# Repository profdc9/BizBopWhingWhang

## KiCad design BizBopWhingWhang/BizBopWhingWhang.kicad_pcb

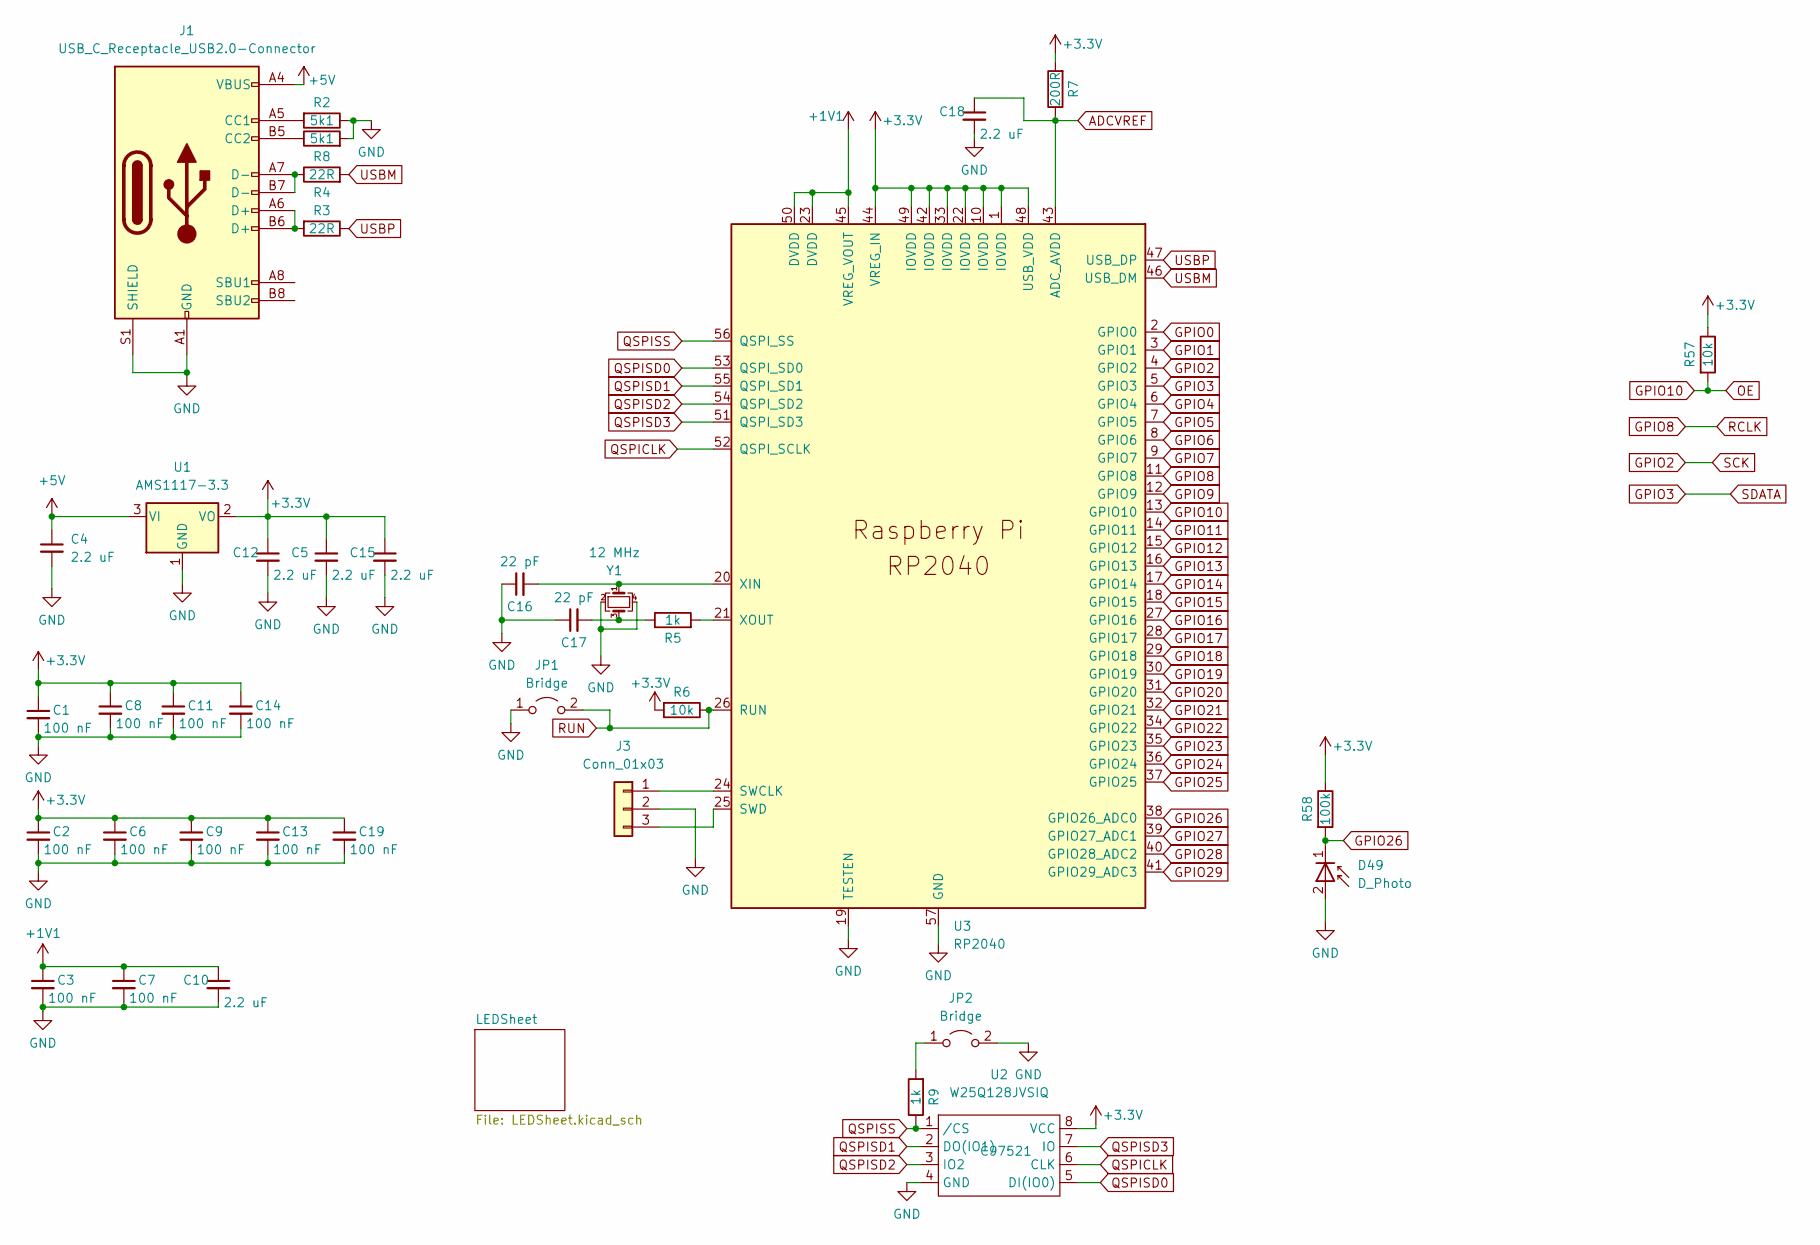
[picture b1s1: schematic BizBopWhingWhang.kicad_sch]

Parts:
C1, C2, C3, C6, C7, C8, C9, C11, C13, C14, C19: 100 nF; C_0402_1005Metric; LCSC C307331
C4, C5, C10, C12, C15, C18: 2.2 uF; C_0603_1608Metric; LCSC C23630
C16, C17: 22 pF; C_0402_1005Metric; LCSC C1555
D49: D_Photo; PD-1522CTR8; LCSC C146236
J1: USB_C_Receptacle_USB2.0-Connector; TYPE-C-31-M-12; LCSC C165948
J3: Conn_01x03; PinHeader_1x03_P2.54mm_Vertical
JP1, JP2: Bridge; PinHeader_1x02_P2.54mm_Vertical
R2, R8: 5k1; R_0603_1608Metric_Pad0.98x0.95mm_HandSolder; LCSC C23186
R3, R4: 22R; R_0603_1608Metric_Pad0.98x0.95mm_HandSolder; LCSC C23345
R5: 1k; R_0402_1005Metric; LCSC C11702
R6, R57: 10k; R_0603_1608Metric_Pad0.98x0.95mm_HandSolder; LCSC C25804
R7: 200R; R_0603_1608Metric_Pad0.98x0.95mm_HandSolder; LCSC C22962
R9: 1k; R_0603_1608Metric_Pad0.98x0.95mm_HandSolder; LCSC C21190
R58: 100k; R_0603_1608Metric_Pad0.98x0.95mm_HandSolder; LCSC C25803
U1: AMS1117-3.3; SOT-223-3_TabPin2; LCSC C6186
U2: W25Q128JVSIQ; SOIC-8_3.9x4.9mm_P1.27mm_mod; LCSC C97521
U3: RP2040; QFN-56-1EP_7x7mm_P0.4mm_EP3.2x3.2mm; LCSC C2040
Y1: 12 MHz; Crystal_SMD_3225-4Pin_3.2x2.5mm; LCSC C9002

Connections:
+1V1: C3.1, C7.1, C10.1, U3.23 (DVDD), U3.45 (VREG_VOUT), U3.50 (DVDD)
+3.3V: C1.1, C2.1, C5.1, C6.1, C8.1, C9.1, C11.1, C12.1, C13.1, C14.1, C15.1, C19.1, R6.2, R7.2, R57.1, R58.1, U1.2 (VO), U2.8 (VCC), U3.1 (IOVDD), U3.10 (IOVDD), U3.22 (IOVDD), U3.33 (IOVDD), U3.42 (IOVDD), U3.44 (VREG_IN), U3.48 (USB_VDD), U3.49 (IOVDD); also elsewhere on the board
+5V: C4.1, J1.A4 (VBUS), J1.A9 (VBUS), J1.B4 (VBUS), J1.B9 (VBUS), U1.3 (VI)
ADCVREF: C18.1, R7.1, U3.43 (ADC_AVDD)
GND: C1.2, C2.2, C3.2, C4.2, C5.2, C6.2, C7.2, C8.2, C9.2, C10.2, C11.2, C12.2, C13.2, C14.2, C15.2, C16.1, C17.1, C18.2, C19.2, D49.2 (A), J1.A1 (GND), J1.A12 (GND), J1.B1 (GND), J1.B12 (GND), J1.S1 (SHIELD), J3.2, JP1.1 (A), JP2.2 (B), R2.1, R8.2, U1.1 (GND), U2.4 (GND), U3.19 (TESTEN), U3.57 (GND), Y1.2, Y1.4; also elsewhere on the board
GPIO0: U3.2 (GPIO0)
GPIO1: U3.3 (GPIO1)
GPIO2: U3.4 (GPIO2); also elsewhere on the board
GPIO3: U3.5 (GPIO3); also elsewhere on the board
GPIO4: U3.6 (GPIO4)
GPIO5: U3.7 (GPIO5)
GPIO6: U3.8 (GPIO6)
GPIO7: U3.9 (GPIO7)
GPIO8: U3.11 (GPIO8); also elsewhere on the board
GPIO9: U3.12 (GPIO9)
GPIO10: R57.2, U3.13 (GPIO10); also elsewhere on the board
GPIO11: U3.14 (GPIO11)
GPIO12: U3.15 (GPIO12)
GPIO13: U3.16 (GPIO13)
GPIO14: U3.17 (GPIO14)
GPIO15: U3.18 (GPIO15)
GPIO16: U3.27 (GPIO16)
GPIO17: U3.28 (GPIO17)
GPIO18: U3.29 (GPIO18)
GPIO19: U3.30 (GPIO19)
GPIO20: U3.31 (GPIO20)
GPIO21: U3.32 (GPIO21)
GPIO22: U3.34 (GPIO22)
GPIO23: U3.35 (GPIO23)
GPIO24: U3.36 (GPIO24)
GPIO25: U3.37 (GPIO25)
GPIO26: D49.1 (K), R58.2, U3.38 (GPIO26_ADC0)
GPIO27: U3.39 (GPIO27_ADC1)
GPIO28: U3.40 (GPIO28_ADC2)
GPIO29: U3.41 (GPIO29_ADC3)
unnamed: C16.2, U3.20 (XIN), Y1.1
unnamed: C17.2, R5.1, Y1.3
unnamed: J1.A5 (CC1), R2.2
unnamed: J1.A6 (D+), J1.B6 (D+), R3.2
unnamed: J1.A7 (D-), J1.B7 (D-), R4.1
unnamed: J1.B5 (CC2), R8.1
unnamed: J3.1, U3.24 (SWCLK)
unnamed: J3.3, U3.25 (SWD)
unnamed: JP2.1 (A), R9.2
unnamed: R5.2, U3.21 (XOUT)
QSPICLK: U2.6 (CLK), U3.52 (QSPI_SCLK)
QSPISD0: U2.5 (DI(IO0)), U3.53 (QSPI_SD0)
QSPISD1: U2.2 (DO(IO1)), U3.55 (QSPI_SD1)
QSPISD2: U2.3 (IO2), U3.54 (QSPI_SD2)
QSPISD3: U2.7 (IO), U3.51 (QSPI_SD3)
QSPISS: R9.1, U2.1 (/CS), U3.56 (QSPI_SS)
RUN: JP1.2 (B), R6.1, U3.26 (RUN)
USBM: R4.2, U3.46 (USB_DM)
USBP: R3.1, U3.47 (USB_DP)

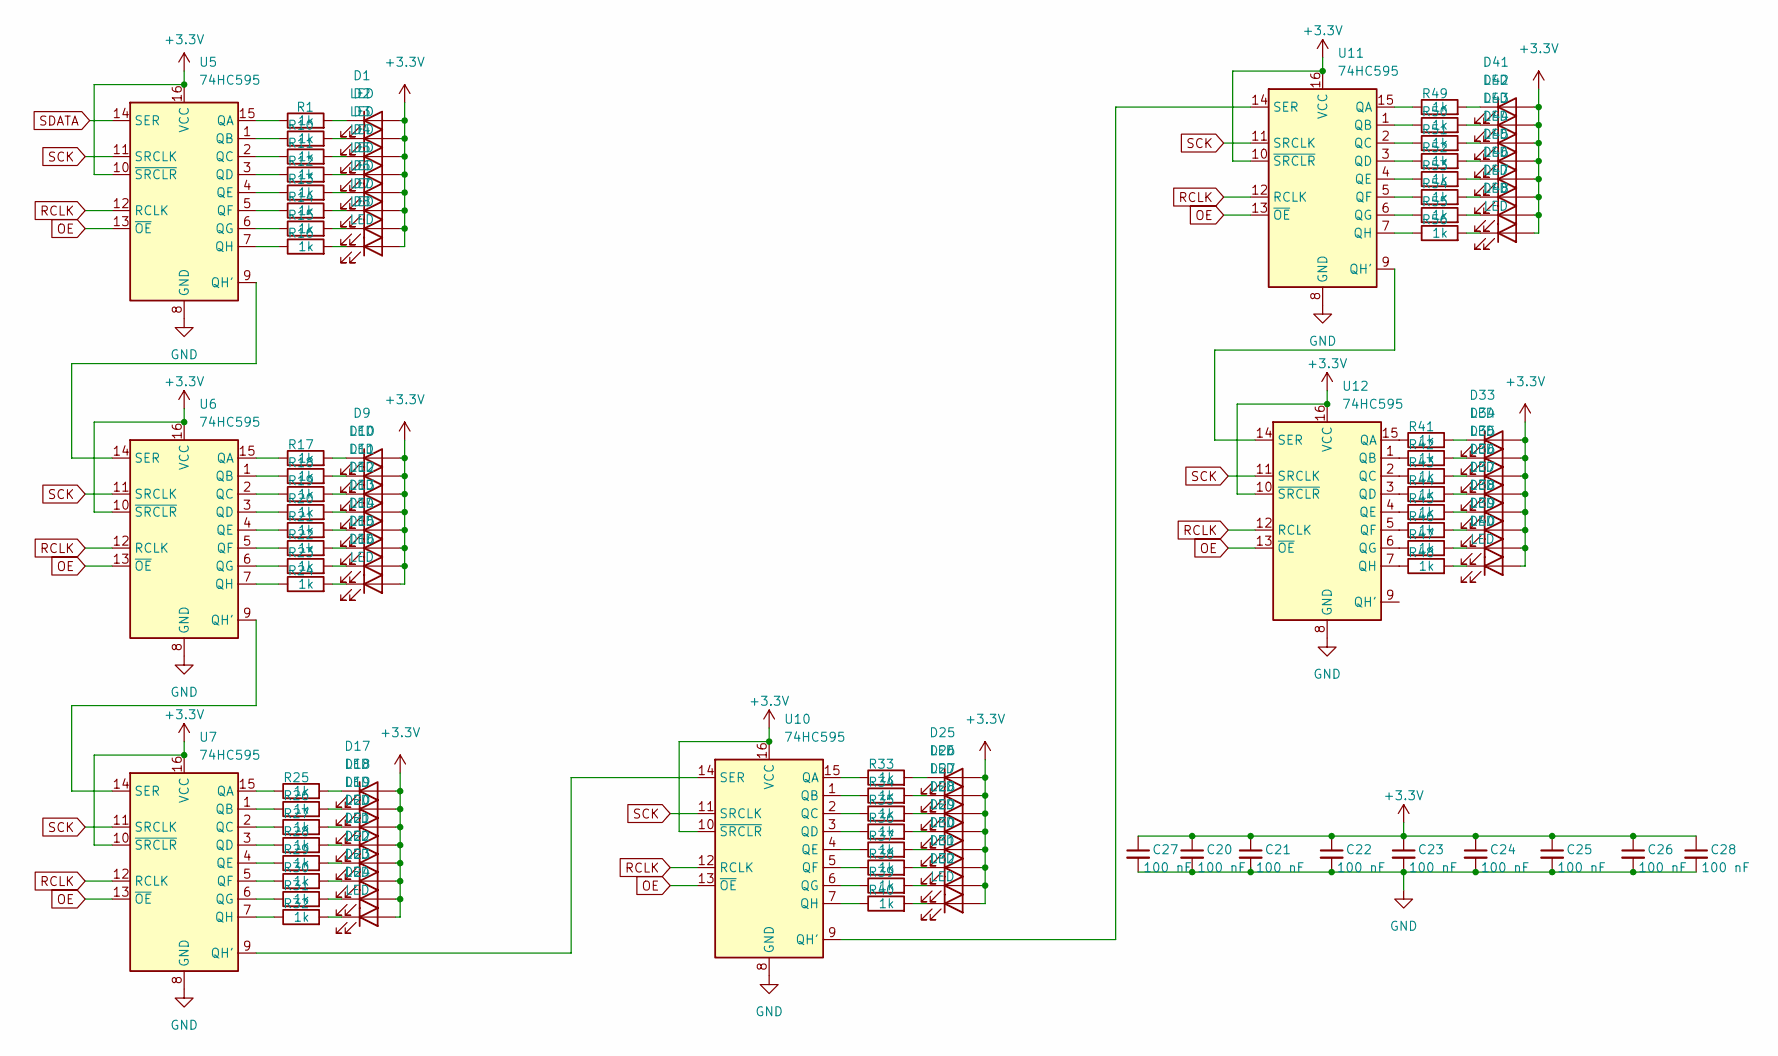
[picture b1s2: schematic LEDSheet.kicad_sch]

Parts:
C20, C21, C22, C23, C24, C25, C26, C27, C28: 100 nF; C_0402_1005Metric; LCSC C307331
D1, D2, D3, D4, D5, D6, D7, D8, D9, D10, D11, D12, D13, D14, D15, D16, D17, D18, D19, D20, D21, D22, D23, D24, D25, D26, D27, D28, D29, D30, D31, D32, D33, D34, D35, D36, D37, D38, D39, D40, D41, D42, D43, D44, D45, D46, D47, D48: LED; LED_0402_1005Metric; LCSC C779449
R1, R10, R11, R12, R13, R14, R15, R16, R17, R18, R19, R20, R21, R22, R23, R24, R25, R26, R27, R28, R29, R30, R31, R32, R33, R34, R35, R36, R37, R38, R39, R40, R41, R42, R43, R44, R45, R46, R47, R48, R49, R50, R51, R52, R53, R54, R55, R56: 1k; R_0402_1005Metric; LCSC C11702
U5, U6, U7, U10, U11, U12: 74HC595; TSSOP-16_4.4x5mm_P0.65mm; LCSC C20613246

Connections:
+3.3V: C20.1, C21.1, C22.1, C23.1, C24.1, C25.1, C26.1, C27.1, C28.1, D1.2 (A), D2.2 (A), D3.2 (A), D4.2 (A), D5.2 (A), D6.2 (A), D7.2 (A), D8.2 (A), D9.2 (A), D10.2 (A), D11.2 (A), D12.2 (A), D13.2 (A), D14.2 (A), D15.2 (A), D16.2 (A), D17.2 (A), D18.2 (A), D19.2 (A), D20.2 (A), D21.2 (A), D22.2 (A), D23.2 (A), D24.2 (A), D25.2 (A), D26.2 (A), D27.2 (A), D28.2 (A), D29.2 (A), D30.2 (A), D31.2 (A), D32.2 (A), D33.2 (A), D34.2 (A), D35.2 (A), D36.2 (A), D37.2 (A), D38.2 (A), D39.2 (A), D40.2 (A), D41.2 (A), D42.2 (A), D43.2 (A), D44.2 (A), D45.2 (A), D46.2 (A), D47.2 (A), D48.2 (A), U5.10 (~SRCLR), U5.16 (VCC), U6.10 (~SRCLR), U6.16 (VCC), U7.10 (~SRCLR), U7.16 (VCC), U10.10 (~SRCLR), U10.16 (VCC), U11.10 (~SRCLR), U11.16 (VCC), U12.10 (~SRCLR), U12.16 (VCC); also elsewhere on the board
GND: C20.2, C21.2, C22.2, C23.2, C24.2, C25.2, C26.2, C27.2, C28.2, U5.8 (GND), U6.8 (GND), U7.8 (GND), U10.8 (GND), U11.8 (GND), U12.8 (GND); also elsewhere on the board
GPIO2: U5.11 (SRCLK), U6.11 (SRCLK), U7.11 (SRCLK), U10.11 (SRCLK), U11.11 (SRCLK), U12.11 (SRCLK); also elsewhere on the board
GPIO3: U5.14 (SER); also elsewhere on the board
GPIO8: U5.12 (RCLK), U6.12 (RCLK), U7.12 (RCLK), U10.12 (RCLK), U11.12 (RCLK), U12.12 (RCLK); also elsewhere on the board
GPIO10: U5.13 (~OE), U6.13 (~OE), U7.13 (~OE), U10.13 (~OE), U11.13 (~OE), U12.13 (~OE); also elsewhere on the board
unnamed: D1.1 (K), R1.2
unnamed: D2.1 (K), R10.2
unnamed: D3.1 (K), R11.2
unnamed: D4.1 (K), R12.2
unnamed: D5.1 (K), R13.2
unnamed: D6.1 (K), R14.2
unnamed: D7.1 (K), R15.2
unnamed: D8.1 (K), R16.2
unnamed: D9.1 (K), R17.2
unnamed: D10.1 (K), R18.2
unnamed: D11.1 (K), R19.2
unnamed: D12.1 (K), R20.2
unnamed: D13.1 (K), R21.2
unnamed: D14.1 (K), R22.2
unnamed: D15.1 (K), R23.2
unnamed: D16.1 (K), R24.2
unnamed: D17.1 (K), R25.2
unnamed: D18.1 (K), R26.2
unnamed: D19.1 (K), R27.2
unnamed: D20.1 (K), R28.2
unnamed: D21.1 (K), R29.2
unnamed: D22.1 (K), R30.2
unnamed: D23.1 (K), R31.2
unnamed: D24.1 (K), R32.2
unnamed: D25.1 (K), R33.2
unnamed: D26.1 (K), R34.2
unnamed: D27.1 (K), R35.2
unnamed: D28.1 (K), R36.2
unnamed: D29.1 (K), R37.2
unnamed: D30.1 (K), R38.2
unnamed: D31.1 (K), R39.2
unnamed: D32.1 (K), R40.2
unnamed: D33.1 (K), R41.2
unnamed: D34.1 (K), R42.2
unnamed: D35.1 (K), R43.2
unnamed: D36.1 (K), R44.2
unnamed: D37.1 (K), R45.2
unnamed: D38.1 (K), R46.2
unnamed: D39.1 (K), R47.2
unnamed: D40.1 (K), R48.2
unnamed: D41.1 (K), R49.2
unnamed: D42.1 (K), R50.2
unnamed: D43.1 (K), R51.2
unnamed: D44.1 (K), R52.2
unnamed: D45.1 (K), R53.2
unnamed: D46.1 (K), R54.2
unnamed: D47.1 (K), R55.2
unnamed: D48.1 (K), R56.2
unnamed: R1.1, U5.15 (QA)
unnamed: R10.1, U5.1 (QB)
unnamed: R11.1, U5.2 (QC)
unnamed: R12.1, U5.3 (QD)
unnamed: R13.1, U5.4 (QE)
unnamed: R14.1, U5.5 (QF)
unnamed: R15.1, U5.6 (QG)
unnamed: R16.1, U5.7 (QH)
unnamed: R17.1, U6.15 (QA)
unnamed: R18.1, U6.1 (QB)
unnamed: R19.1, U6.2 (QC)
unnamed: R20.1, U6.3 (QD)
unnamed: R21.1, U6.4 (QE)
unnamed: R22.1, U6.5 (QF)
unnamed: R23.1, U6.6 (QG)
unnamed: R24.1, U6.7 (QH)
unnamed: R25.1, U7.15 (QA)
unnamed: R26.1, U7.1 (QB)
unnamed: R27.1, U7.2 (QC)
unnamed: R28.1, U7.3 (QD)
unnamed: R29.1, U7.4 (QE)
unnamed: R30.1, U7.5 (QF)
unnamed: R31.1, U7.6 (QG)
unnamed: R32.1, U7.7 (QH)
unnamed: R33.1, U10.15 (QA)
unnamed: R34.1, U10.1 (QB)
unnamed: R35.1, U10.2 (QC)
unnamed: R36.1, U10.3 (QD)
unnamed: R37.1, U10.4 (QE)
unnamed: R38.1, U10.5 (QF)
unnamed: R39.1, U10.6 (QG)
unnamed: R40.1, U10.7 (QH)
unnamed: R41.1, U12.15 (QA)
unnamed: R42.1, U12.1 (QB)
unnamed: R43.1, U12.2 (QC)
unnamed: R44.1, U12.3 (QD)
unnamed: R45.1, U12.4 (QE)
unnamed: R46.1, U12.5 (QF)
unnamed: R47.1, U12.6 (QG)
unnamed: R48.1, U12.7 (QH)
unnamed: R49.1, U11.15 (QA)
unnamed: R50.1, U11.1 (QB)
unnamed: R51.1, U11.2 (QC)
unnamed: R52.1, U11.3 (QD)
unnamed: R53.1, U11.4 (QE)
unnamed: R54.1, U11.5 (QF)
unnamed: R55.1, U11.6 (QG)
unnamed: R56.1, U11.7 (QH)
unnamed: U5.9 (QH'), U6.14 (SER)
unnamed: U6.9 (QH'), U7.14 (SER)
unnamed: U10.9 (QH'), U11.14 (SER)
unnamed: U7.9 (QH'), U10.14 (SER)
unnamed: U11.9 (QH'), U12.14 (SER)

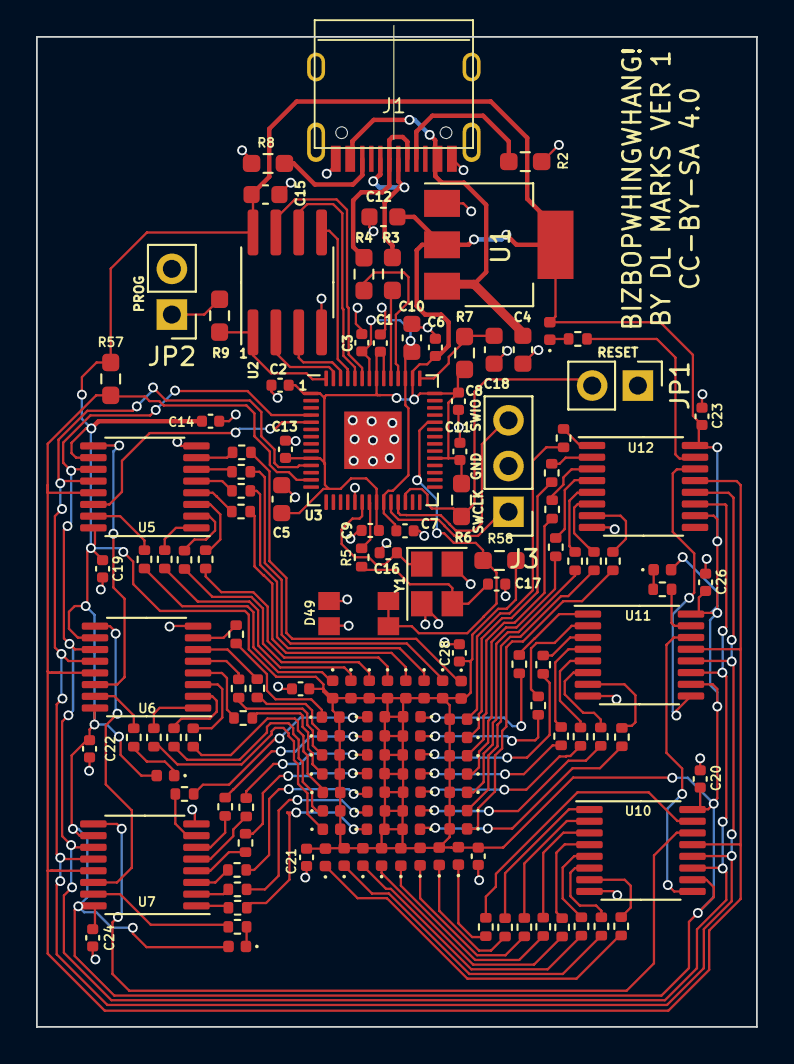
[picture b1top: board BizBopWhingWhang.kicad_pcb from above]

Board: 2 copper layers, 40.0 x 55.0 mm, 149 parts (0 on the bottom side), 130 nets.

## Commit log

2024-07-02 Latest version
2024-07-23 JLCPCB 2024-07-20
2024-08-11 Added first draft of code

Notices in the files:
BizBopWhingWhang/BizBopWhingWhang.kicad_pcb:
CC-BY-SA 4.0
